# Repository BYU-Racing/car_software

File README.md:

# Car Software

## UML Diagram

See the UML diagram [here](/VehicleCode/CarUML_v1.0.md)

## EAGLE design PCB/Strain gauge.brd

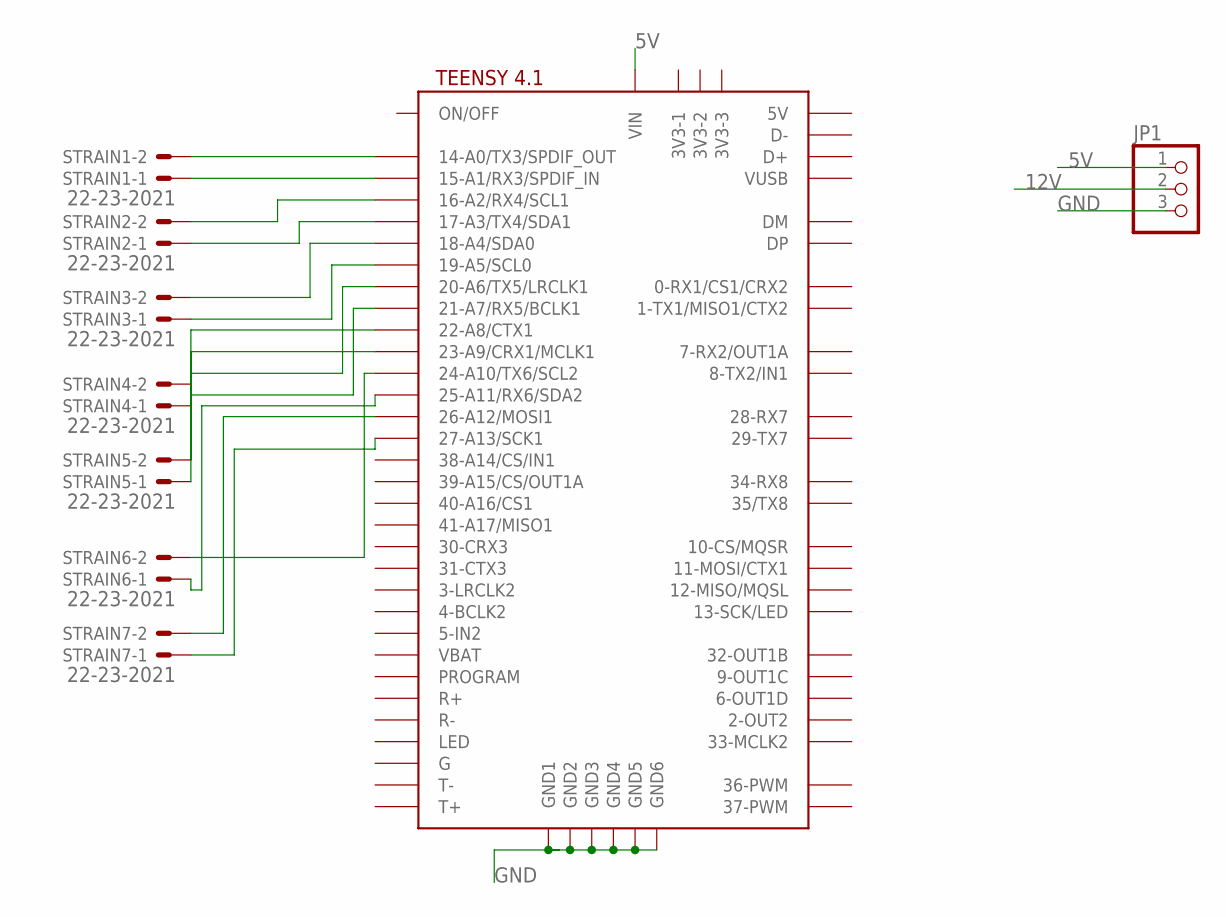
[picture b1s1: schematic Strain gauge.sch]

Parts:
JP1: PINHD-1X3; 1X03
STRAIN1, STRAIN2, STRAIN3, STRAIN4, STRAIN5, STRAIN6, STRAIN7: 22-23-2021
U$1: TEENSY41

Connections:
5V: JP1.1, U$1.VIN
12V: JP1.2
GND: JP1.3, U$1.GND1, U$1.GND2, U$1.GND3, U$1.GND4, U$1.GND5, U$1.GND6
unnamed: STRAIN1.2, U$1.14-A0/TX3/SPDIF_OUT
unnamed: STRAIN1.1, U$1.15-A1/RX3/SPDIF_IN
unnamed: STRAIN2.2, U$1.16-A2/RX4/SCL1
unnamed: STRAIN2.1, U$1.17-A3/TX4/SDA1
unnamed: STRAIN3.2, U$1.18-A4/SDA0
unnamed: STRAIN3.1, U$1.19-A5/SCL0
unnamed: STRAIN4.2, U$1.20-A6/TX5/LRCLK1
unnamed: STRAIN4.1, U$1.21-A7/RX5/BCLK1
unnamed: STRAIN5.2, U$1.22-A8/CTX1
unnamed: STRAIN5.1, U$1.23-A9/CRX1/MCLK1
unnamed: STRAIN6.2, U$1.24-A10/TX6/SCL2
unnamed: STRAIN6.1, U$1.25-A11/RX6/SDA2
unnamed: STRAIN7.2, U$1.26-A12/MOSI1
unnamed: STRAIN7.1, U$1.27-A13/SCK1

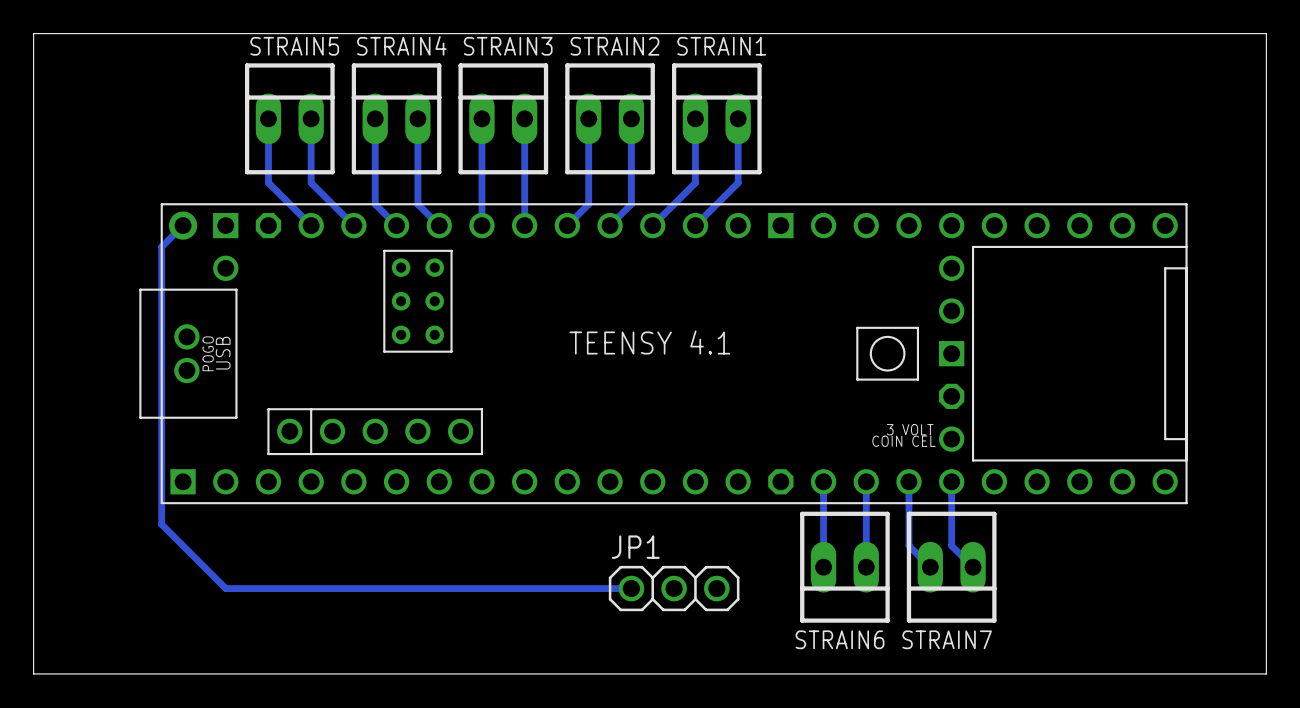
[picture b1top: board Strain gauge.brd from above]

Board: 2 copper layers, 73.3 x 38.1 mm, 9 parts (0 on the bottom side), 16 nets.

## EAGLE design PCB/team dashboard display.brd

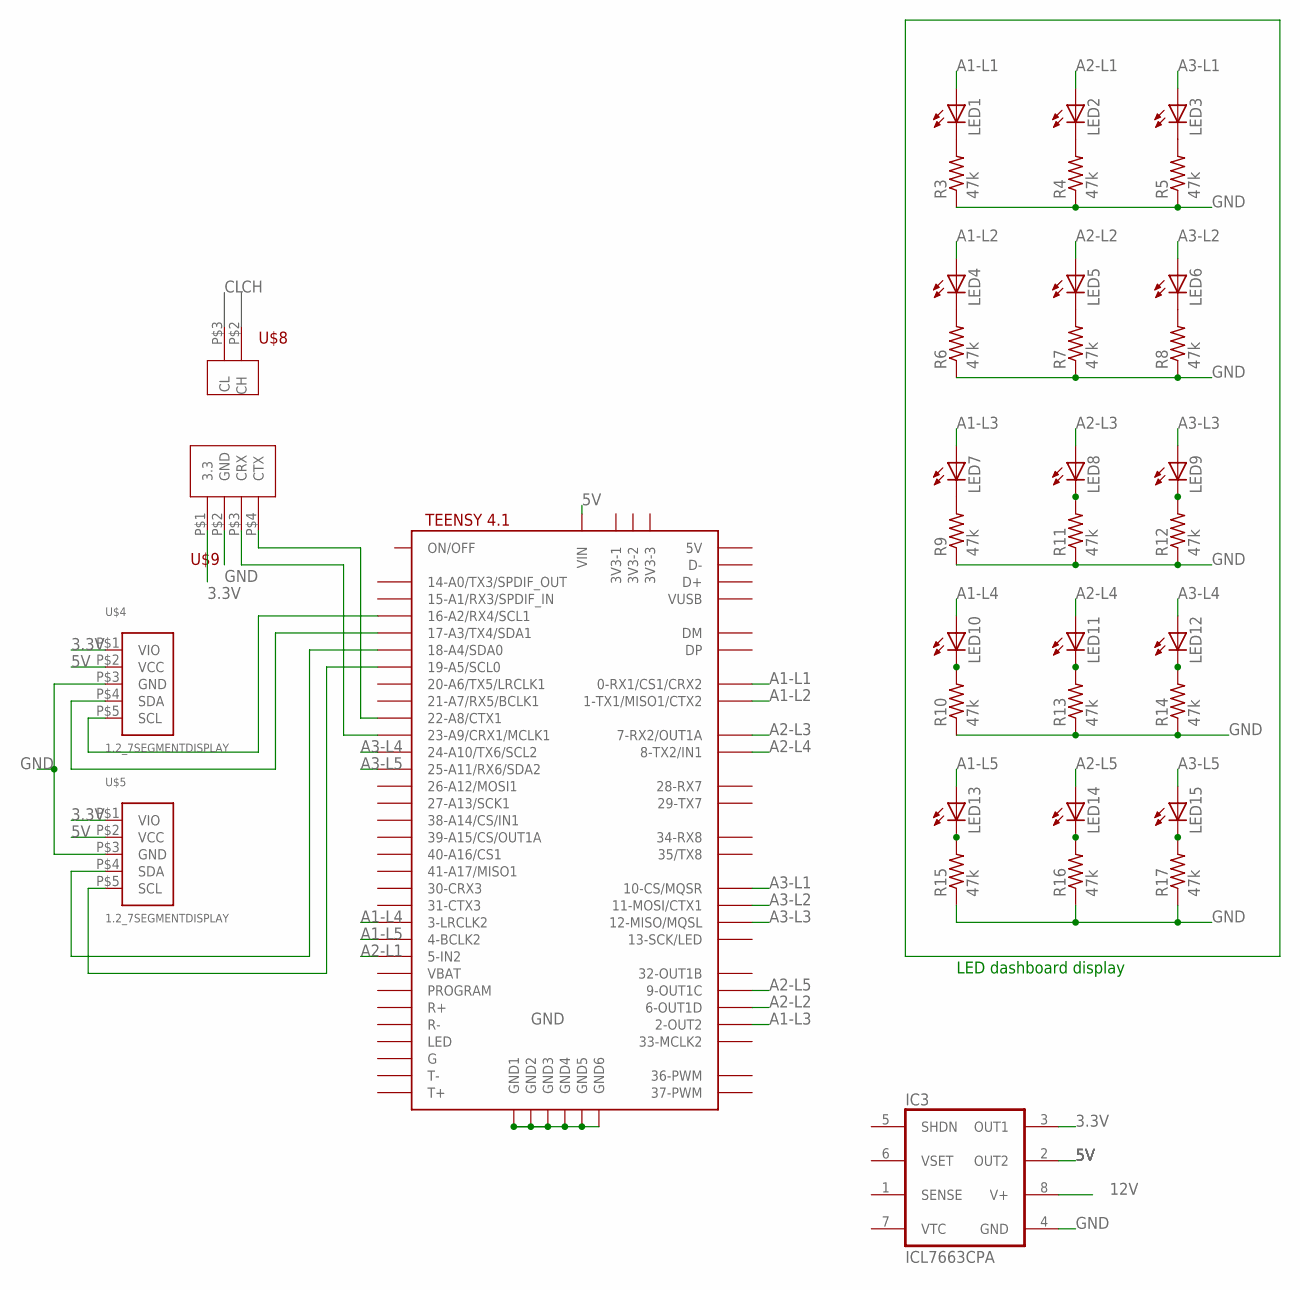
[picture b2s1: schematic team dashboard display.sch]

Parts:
IC3: ICL7663CPA; DIL08
LED1, LED2, LED3, LED4, LED5, LED6, LED7, LED8, LED9, LED10, LED11, LED12, LED13, LED14, LED15: LED3MM
R3, R4, R5, R6, R7, R8, R9, R10, R11, R12, R13, R14, R15, R16, R17: 47k; 0204/7
U$2: TEENSY41
U$4, U$5: 1.2_7SEGMENTDISPLAY; 5IL
U$8: CAN_BUS
U$9: CAN_TEE; CAN_TEN

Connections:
3.3V: IC3.3 (OUT1), U$4.P$1 (VIO), U$5.P$1 (VIO), U$9.P$1 (3.3)
5V: IC3.2 (OUT2), U$2.VIN, U$4.P$2 (VCC), U$5.P$2 (VCC); also elsewhere on the board
A1-L1: LED1.A, U$2.0-RX1/CS1/CRX2
A1-L2: LED4.A, U$2.1-TX1/MISO1/CTX2
A1-L3: LED7.A, U$2.2-OUT2
A1-L4: LED10.A, U$2.3-LRCLK2
A1-L5: LED13.A, U$2.4-BCLK2
A2-L1: LED2.A, U$2.5-IN2
A2-L2: LED5.A, U$2.6-OUT1D
A2-L3: LED8.A, U$2.7-RX2/OUT1A
A2-L4: LED11.A, U$2.8-TX2/IN2 (8-TX2/IN1)
A2-L5: LED14.A, U$2.9-OUT1C
A3-L1: LED3.A, U$2.10-CS\MQSR (10-CS/MQSR)
A3-L2: LED6.A, U$2.11-MOSI/CTX1
A3-L3: LED9.A, U$2.12-MISO/MQSL
A3-L4: LED12.A, U$2.24-A10/TX6/SCL2
A3-L5: LED15.A, U$2.25-A11/RX6/SDA2
GND: IC3.4 (GND), R3.1, R4.1, R5.1, R6.1, R7.1, R8.1, R9.1, R10.1, R11.1, R12.1, R13.1, R14.1, R15.1, R16.1, R17.1, U$2.GND1, U$2.GND2, U$2.GND3, U$2.GND4, U$2.GND5, U$2.GND6, U$4.P$3 (GND), U$5.P$3 (GND), U$9.P$2 (GND); also elsewhere on the board
unnamed: U$2.17-A3/TX4/SDA1, U$4.P$4 (SDA)
unnamed: U$2.16-A2/RX4/SCL1, U$4.P$5 (SCL)
unnamed: U$2.18-A4/SDA0, U$5.P$4 (SDA)
unnamed: U$2.19-A5/SCL0, U$5.P$5 (SCL)
unnamed: LED1.K (C), R3.2
unnamed: LED2.K (C), R4.2
unnamed: U$2.22-A8/CTX1, U$9.P$4 (CTX)
unnamed: U$2.23-A9/CRX1/MCLK1, U$9.P$3 (CRX)
unnamed: LED3.K (C), R5.2
unnamed: LED4.K (C), R6.2
unnamed: LED5.K (C), R7.2
unnamed: LED6.K (C), R8.2
unnamed: LED7.K (C), R9.2
unnamed: LED10.K (C), R10.2
unnamed: LED8.K (C), R11.2
unnamed: LED9.K (C), R12.2
unnamed: LED11.K (C), R13.2
unnamed: LED12.K (C), R14.2
unnamed: LED13.K (C), R15.2
unnamed: LED14.K (C), R16.2
unnamed: LED15.K (C), R17.2

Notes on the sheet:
LED dashboard display

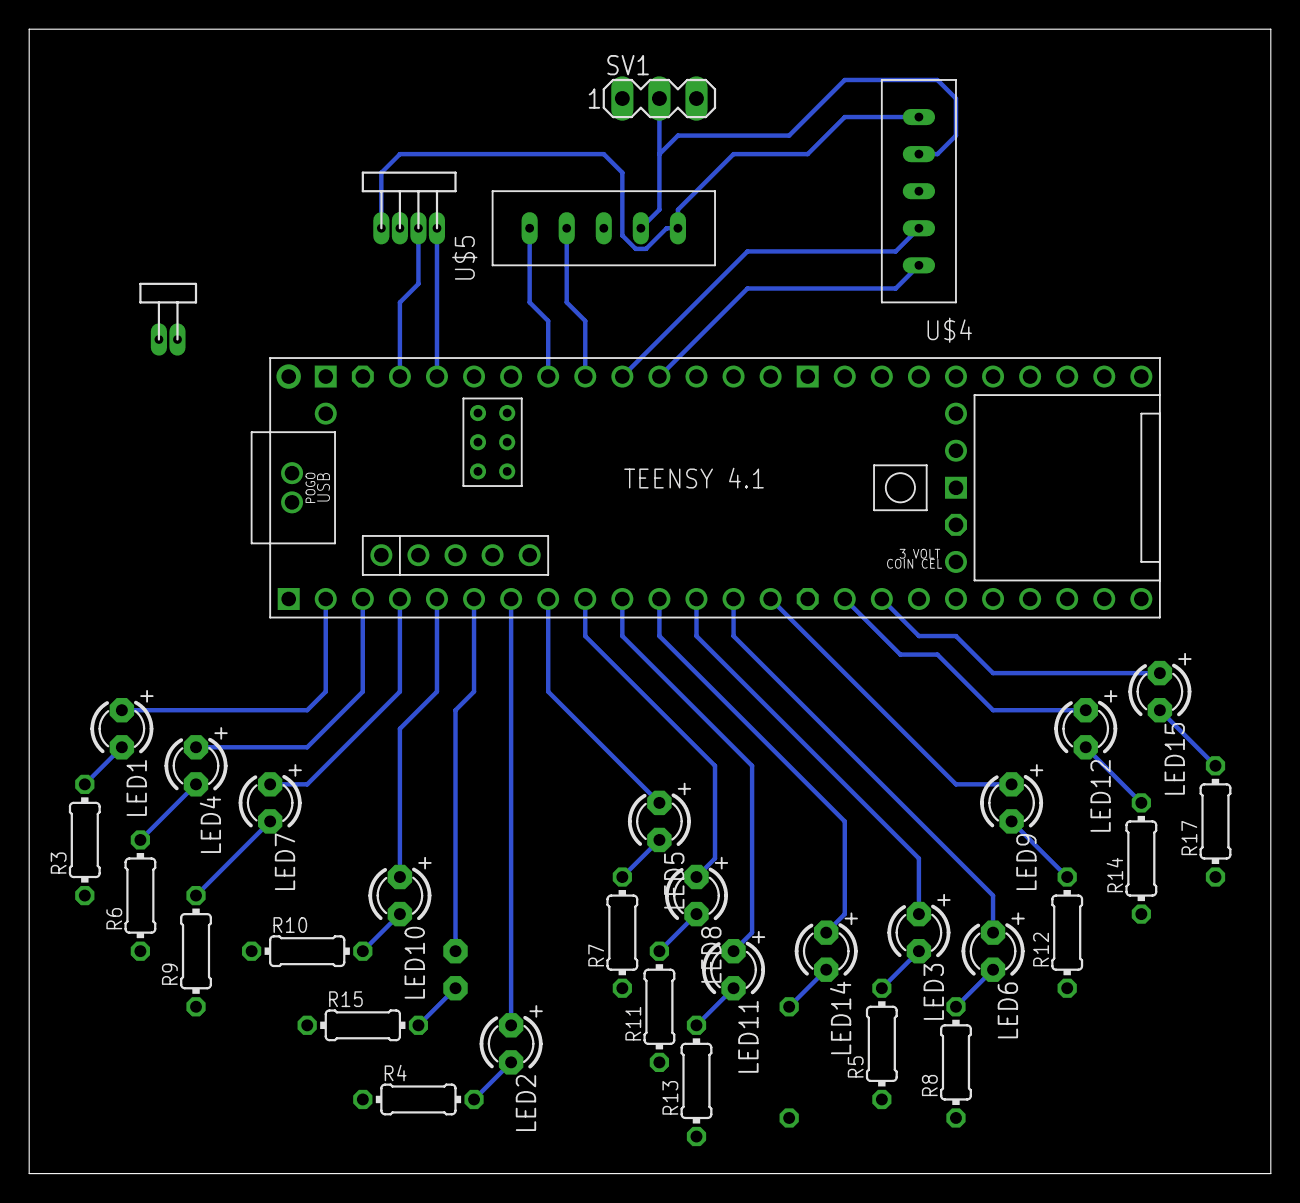
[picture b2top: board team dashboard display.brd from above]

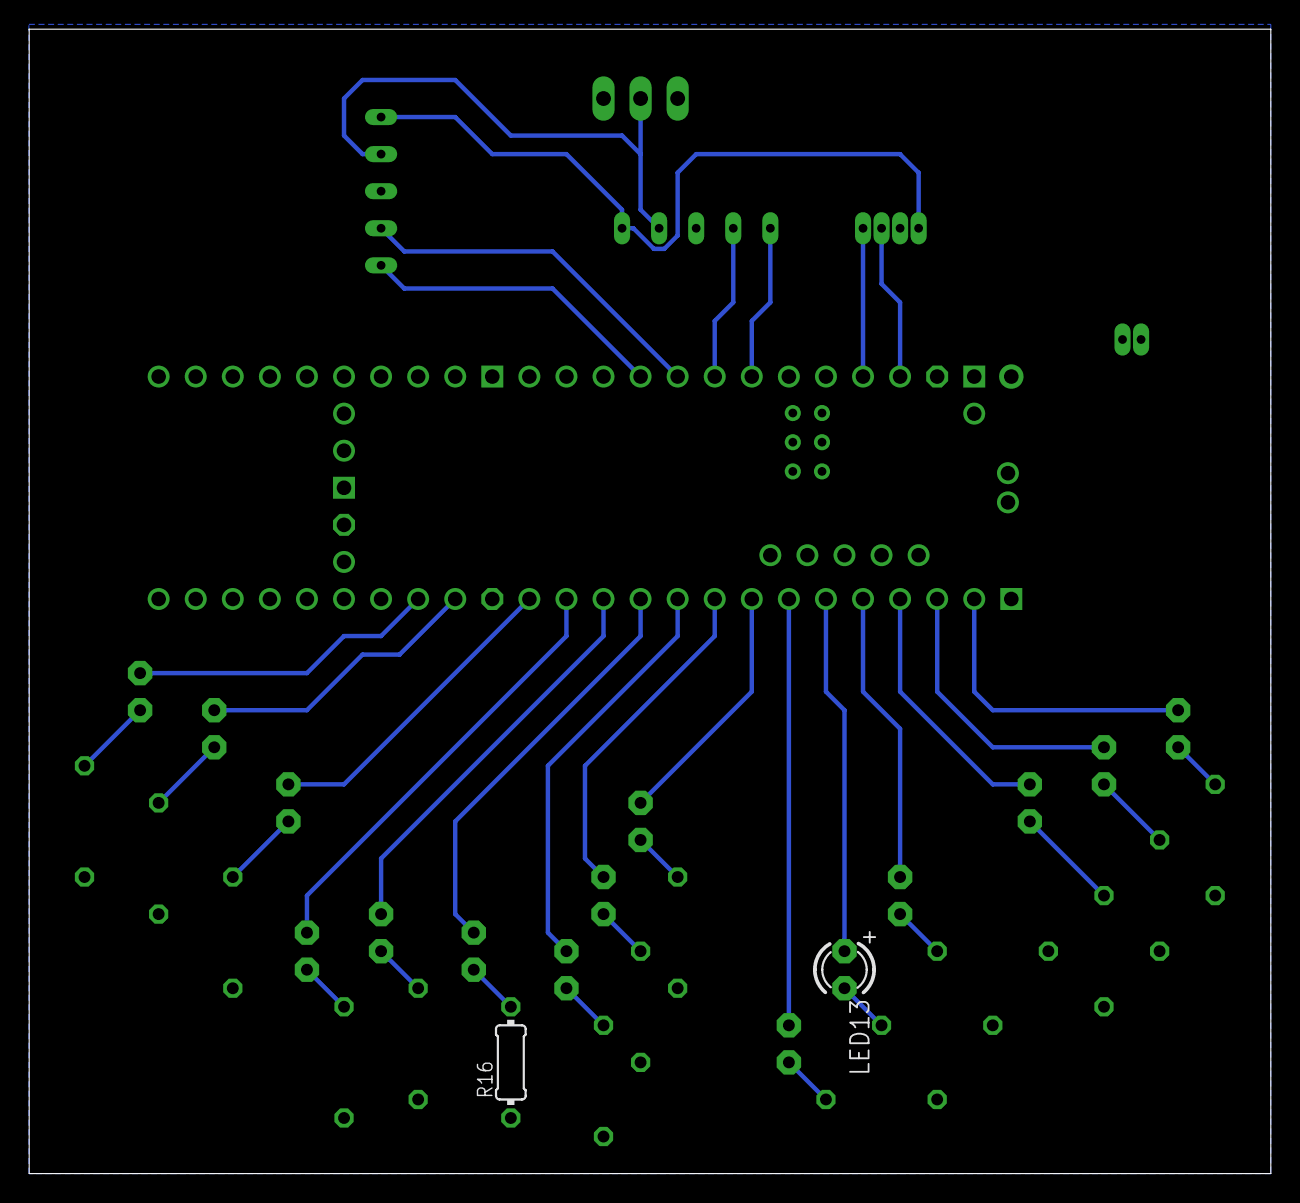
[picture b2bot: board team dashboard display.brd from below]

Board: 2 copper layers, 85.1 x 78.4 mm, 36 parts (2 on the bottom side), 39 nets.

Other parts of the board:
SV1: MA03-1

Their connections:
5V: SV1.2; also elsewhere on the board
GND: SV1.1; also elsewhere on the board

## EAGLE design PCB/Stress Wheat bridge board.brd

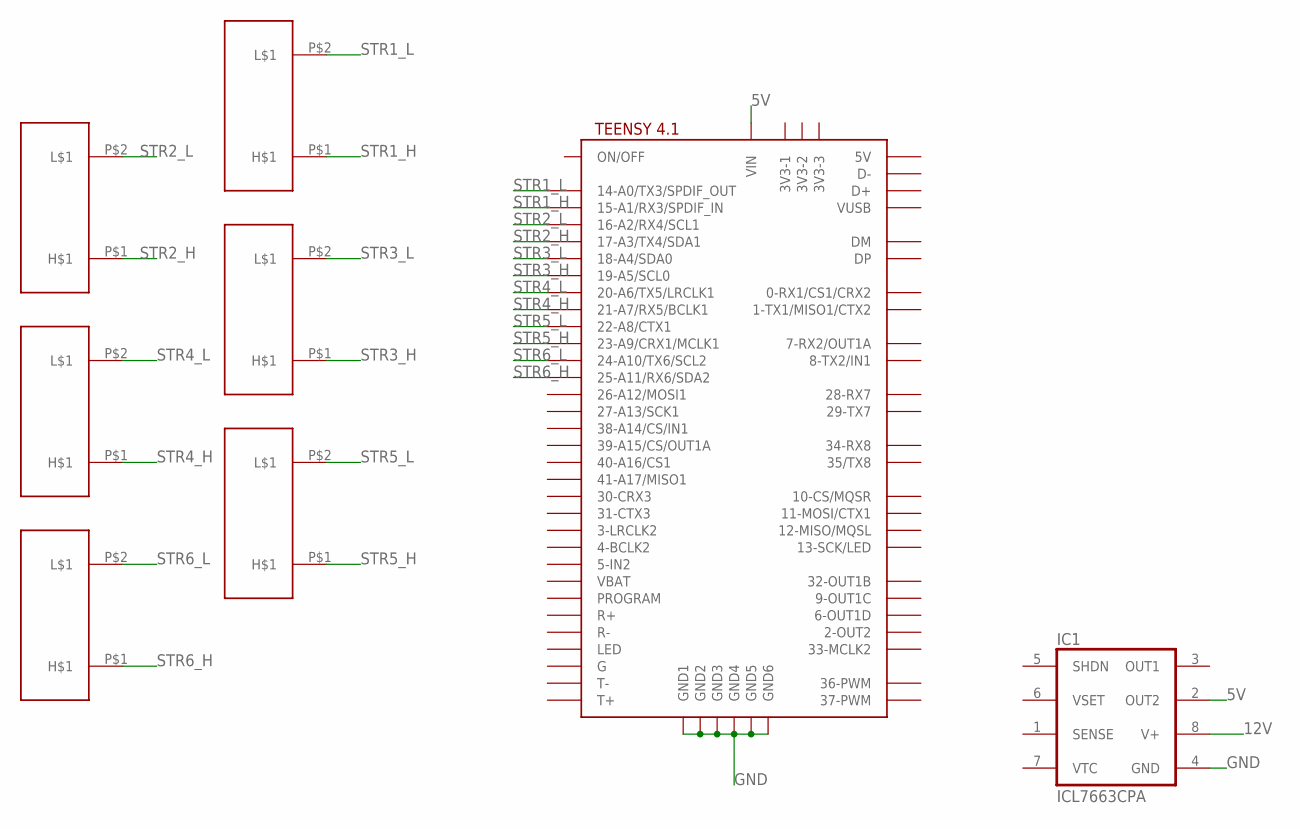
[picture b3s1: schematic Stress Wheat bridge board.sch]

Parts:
IC1: ICL7663CPA; DIL08
U$1, U$2, U$4, U$5, U$6, U$7: STR_GAUGE
U$3: TEENSY41

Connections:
5V: IC1.2 (OUT2), U$3.VIN
12V: IC1.8 (V+)
GND: IC1.4 (GND), U$3.GND1, U$3.GND2, U$3.GND3, U$3.GND4, U$3.GND5, U$3.GND6
STR1_H: U$1.P$1, U$3.15-A1/RX3/SPDIF_IN
STR1_L: U$1.P$2, U$3.14-A0/TX3/SPDIF_OUT
STR2_H: U$2.P$1, U$3.17-A3/TX4/SDA1
STR2_L: U$2.P$2, U$3.16-A2/RX4/SCL1
STR3_H: U$3.19-A5/SCL0, U$4.P$1
STR3_L: U$3.18-A4/SDA0, U$4.P$2
STR4_H: U$3.21-A7/RX5/BCLK1, U$5.P$1
STR4_L: U$3.20-A6/TX5/LRCLK1, U$5.P$2
STR5_H: U$3.23-A9/CRX1/MCLK1, U$6.P$1
STR5_L: U$3.22-A8/CTX1, U$6.P$2
STR6_H: U$3.25-A11/RX6/SDA2, U$7.P$1
STR6_L: U$3.24-A10/TX6/SCL2, U$7.P$2

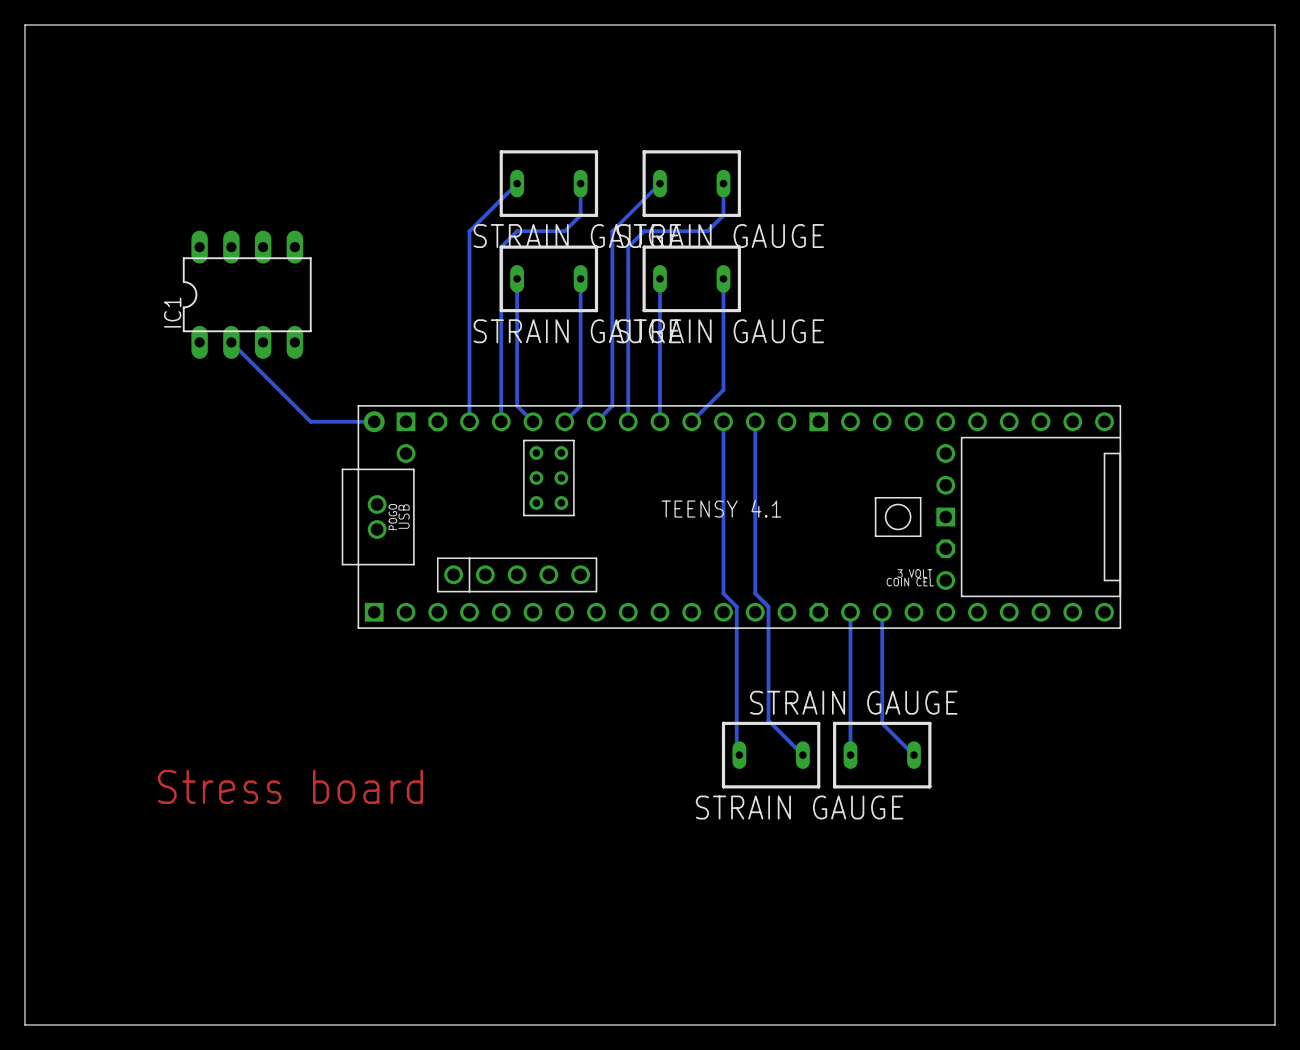
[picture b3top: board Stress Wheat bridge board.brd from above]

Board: 2 copper layers, 100.0 x 80.0 mm, 8 parts (0 on the bottom side), 14 nets.

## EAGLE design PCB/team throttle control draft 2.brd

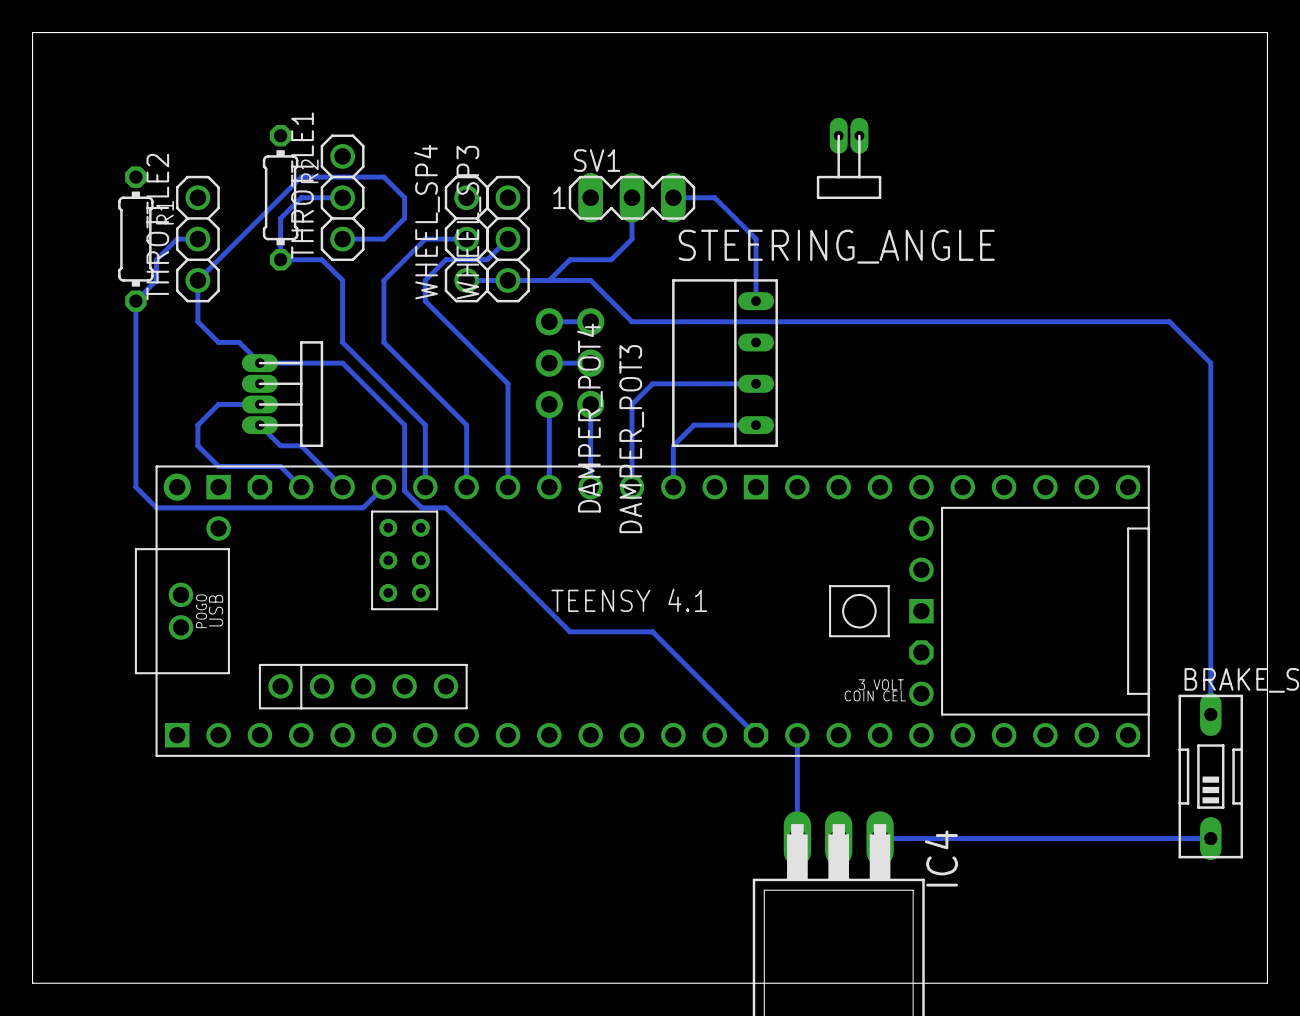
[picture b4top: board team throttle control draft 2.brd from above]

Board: 2 copper layers, 75.9 x 58.4 mm, 15 parts (0 on the bottom side), 18 nets.

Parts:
BRAKE_SW: EDG-01
DAMPER_POT3, DAMPER_POT4: 1X03-CLEANBIG
IC4: 7805T; TO220H
R1: 47k; 0204/7
R2: 470k; 0204/7
STEERING_ANGLE: ROTARY_ENCODER
SV1: MA03-1
THROTTLE1, THROTTLE2: 1X03
U$3: TEENSY41
U$10: CAN_BUS
U$11: CAN_TEE; CAN_TEN
WHEEL_SP3, WHEEL_SP4: 1X03

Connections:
3.3V: THROTTLE1.1, THROTTLE2.1, U$3.3V3-1, U$11.P$1
5V: STEERING_ANGLE.VCC, SV1.3
12V: BRAKE_SW.2, SV1.2, WHEEL_SP3.1, WHEEL_SP4.1
A2_2: DAMPER_POT3.3, U$3.16-A2/RX4/SCL1
A3_2: DAMPER_POT4.3, U$3.17-A3/TX4/SDA1
ACC_DATA_OUT_1: R2.2, THROTTLE1.2, U$3.20-A6/TX5/LRCLK1
ACC_DATA_OUT_2: R1.2, THROTTLE2.2, U$3.21-A7/RX5/BCLK1
BL_GND: DAMPER_POT3.2, DAMPER_POT4.2
BR_SW: IC4.3, U$3.24-A10/TX6/SCL2
BR_VCC: DAMPER_POT3.1, DAMPER_POT4.1
CRX_2: U$3.23-A9/CRX1/MCLK1, U$11.P$3
CTX_2: U$3.22-A8/CTX1, U$11.P$4
GND: IC4.2, R1.1, R2.1, STEERING_ANGLE.GND, SV1.1, THROTTLE1.3, THROTTLE2.3, U$3.GND1, U$3.GND2, U$3.GND3, U$3.GND4, U$3.GND5, U$3.GND6, WHEEL_SP3.3, WHEEL_SP4.3
unnamed: BRAKE_SW.1, IC4.1
T2_DP_1: STEERING_ANGLE.PH_A, U$3.14-A0/TX3/SPDIF_OUT
T2_DP_2: STEERING_ANGLE.PH_B, U$3.15-A1/RX3/SPDIF_IN
WH_SP3_D: U$3.18-A4/SDA0, WHEEL_SP3.2
WH_SP4_D: U$3.19-A5/SCL0, WHEEL_SP4.2

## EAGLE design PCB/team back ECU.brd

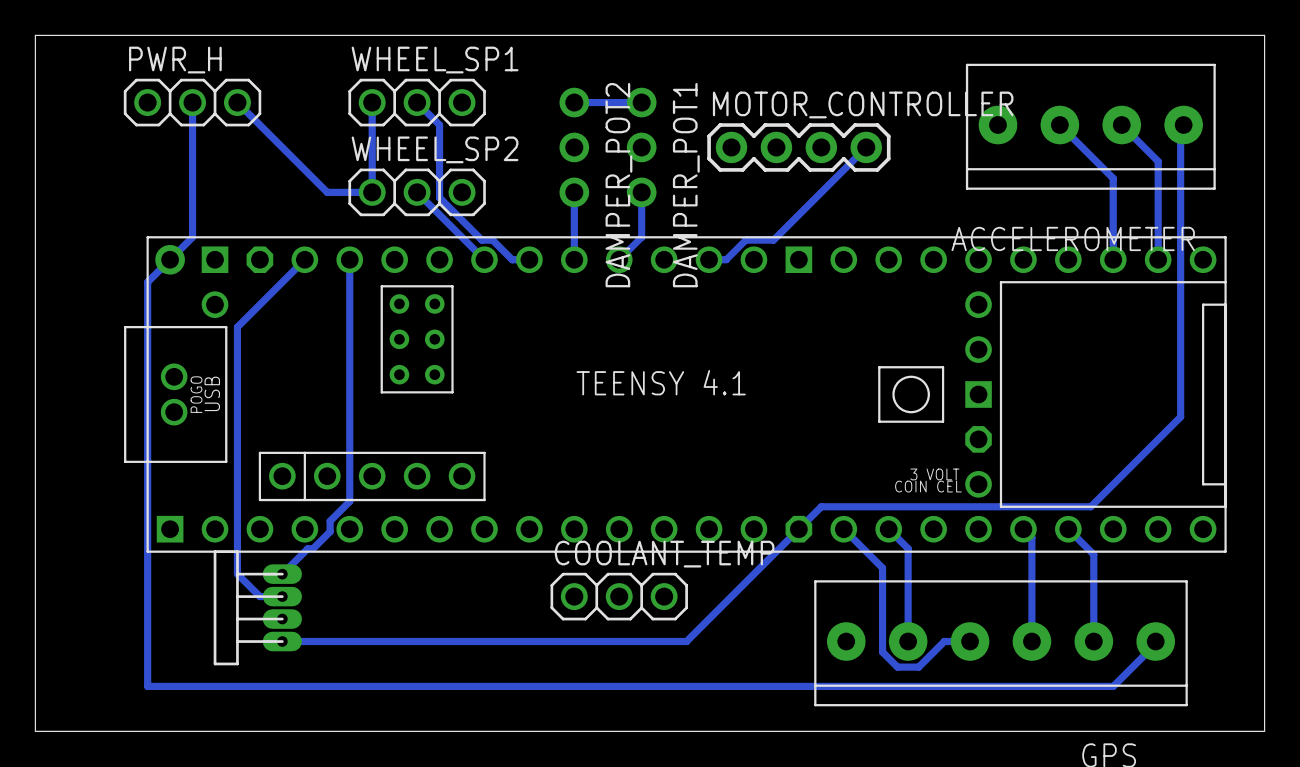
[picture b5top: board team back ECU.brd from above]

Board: 2 copper layers, 69.5 x 39.4 mm, 11 parts (0 on the bottom side), 18 nets.

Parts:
ACCELEROMETER: 1X4-3.5MM; 1X04-3.5MM
CAN1_TEE: CAN_TEE; CAN_TEN
COOLANT_TEMP: 1X03
DAMPER_POT1, DAMPER_POT2: 1X03-CLEANBIG
GPS: 1X06-3.5MM
MOTOR_CONTROLLER: 1X4-BIG; 1X04-BIG
PWR_H: 1X03
U$1: TEENSY41
WHEEL_SP1, WHEEL_SP2: 1X03

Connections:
3.3V: ACCELEROMETER.4, CAN1_TEE.P$1, U$1.3V3-1
5V: GPS.6, PWR_H.2, U$1.VIN
12V: PWR_H.3, WHEEL_SP1.1, WHEEL_SP2.1
A2: DAMPER_POT1.3, U$1.16-A2/RX4/SCL1
A3: DAMPER_POT2.3, U$1.17-A3/TX4/SDA1
A_MC: MOTOR_CONTROLLER.4, U$1.14-A0/TX3/SPDIF_OUT
BR_VCC: DAMPER_POT1.1, DAMPER_POT2.1
GND: ACCELEROMETER.1, CAN1_TEE.P$2, COOLANT_TEMP.3, DAMPER_POT1.2, DAMPER_POT2.2, GPS.1, MOTOR_CONTROLLER.1, PWR_H.1, U$1.GND1, U$1.GND2, U$1.GND3, U$1.GND4, U$1.GND5, U$1.GND6, WHEEL_SP1.3, WHEEL_SP2.3
unnamed: CAN1_TEE.P$3, U$1.23-A9/CRX1/MCLK1
unnamed: CAN1_TEE.P$4, U$1.22-A8/CTX1
RX: ACCELEROMETER.2, U$1.35-TX8
RX_2: GPS.5, U$1.29-TX7
SCL: GPS.3, U$1.24-A10/TX6/SCL2
SDA: GPS.2, U$1.25-A11/RX6/SDA2
TX: ACCELEROMETER.3, U$1.34-RX8
TX_2: GPS.4, U$1.28-RX7
WH_SP1_D: U$1.18-A4/SDA0, WHEEL_SP1.2
WH_SP2_D: U$1.19-A5/SCL0, WHEEL_SP2.2

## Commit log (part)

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2023-03-30 Fix resize bug, remove magic numbers, text resizes now
2023-03-30 Fix moving text bug
2023-03-30 Functional ready statement
2023-04-02 Attempt animation and fail
2023-04-03 uploaded example data
    follows the format sensorId, timestamp, data. This data comes from the accelerator pedal.
2023-04-04 Attempt to optimize and fail
2023-04-04 Code for sending and Receiving on 1 teensy
2023-04-06 Draft new data reading method
2023-04-08 Add requirements.txt
2023-04-16 Bought new transceiver, sends can msg to self
2023-04-17 Working on reading can message and spinning motor
2023-04-18 FUDGE YEAH
2023-04-18 Reorganization
2023-04-18 Improved Professionalism
2023-04-18 Included Authors
2023-06-03 Added Github_test.m as a test
2023-06-03 Added acceleration modeling Matlab files
2023-07-04 Added a 2nd vehicle profile
2023-07-04 Create README CHECKOUT
2023-07-04 Add files via upload
    original upload
2023-07-08 Teensy 4.1 layout
2023-07-08 Checkout
2023-07-09 Update README CHECKOUT
2023-07-09 7 Segment Displays add
2023-07-09 first draft layout 07-08
2023-09-19 UML Diagram
2023-09-19 trying to fix it
2023-09-20 UML Refinements
2023-09-22 individual boards 1
    Individual boards from the large build of the ECU and throttle control
2023-09-26 sync
2023-09-26 set up empty file structure
2023-09-26 draft input h files
2023-09-26 draft h files for output
2023-09-26 Adjusted file structure
2023-09-26 File Restructuring
2023-09-26 Created ECU Project
2023-09-26 Created other teensy project folders
2023-09-26 Reviewed Car UML
2023-09-26 Small Fix
2023-09-28 Added the team dashboard display schematic and the custom library used for most of the sensors in the schematics.
2023-09-28 clean up comments
2023-09-28 remove unnecessary cpp file
2023-09-28 Refinements
2023-09-28 TODO added
2023-09-29 AnalogSensor Initial work
2023-09-29 Header Comment info
2023-09-29 Comments to guide what to do next
2023-09-29 protected Sensor, analogSensor Update
2023-09-30 analogSensor Type Conversion Fixes
2023-10-02 Got rid of TODO
2023-10-02 Adjusted Sensor Class
2023-10-02 Changes for analog sensor
2023-10-02 team throttle control draft 1
    First draft of the throttle control for review and comments. I am planning on doing a more comprehensive redesign in the coming days.
2023-10-03 team throttle control draft 2
    An updated team throttle control design, streamlined and better routing.
2023-10-03 SensorData class wrk
2023-10-03 draft datacollector
2023-10-03 add docstrings and update uml
2023-10-05 begin .cpp file
2023-10-05 implementing more uart.cpp file
2023-10-05 changes for two serial reads uart.cpp
2023-10-05 Checked
2023-10-06 create and wire dash schematic
2023-10-06 intial commit
2023-10-06 test
2023-10-06 json changes
2023-10-06 changes to uart.cpp
2023-10-08 Draft dashboard.cpp
2023-10-08 add todo
2023-10-08 fix memory leaks and add docstrings
2023-10-09 Initial Servo code
2023-10-09 Started working on Car Class
2023-10-09 Checked and added comments
2023-10-09 added necessary files to data collector 1
2023-10-09 Started data colloctor 1 teensy code
2023-10-09 Reviewed
2023-10-09 Small syntax thing
2023-10-09 It was missing two connections so this is now fixed and fully operating design
2023-10-10 minor changes for merge, dallin
2023-10-10 experiment with object for sensor id
2023-10-10 cleanest id implementation so far
2023-10-10 ready to test all except constructor
2023-10-11 Added Calibration and Testing Folder
2023-10-14 Added Screen Ic2
2023-10-16 Stress board for Wheat bridge and edits
    Created the Wheat bridge board with the different stress gauges in the F-E library. There were some minor edits that the other boards needed as well.
2023-10-16 Updated 10-16-23
2023-10-16 Edited out some issues (10-16-32)
2023-10-16 Added purdy picture (10-16-23)
2023-10-18 small update on throttle
2023-10-24 draft digital sensor
2023-10-27 progess
2023-11-03 Fixed some stuff
2023-11-07 Sensor Classes tested. Needs destructors
2023-12-08 simplified readytocheck
2023-12-08 added 3-pin header to dashboard display pcb/schematic. optimized component layout and shrunk pcb board by 40-50%
2023-12-11 Altium conversion
    Converted all PCB files from EAGLE to Altium. Many bugs need to be ironed out on each board/schem but it's likely a simple process
2024-01-09 Updated ECU and Strain Gauge board
2024-01-10 Remove voltage regulator. Add 3-pin header. Connect 3.3V wire
2024-01-11 ThrottleWrite written
2024-01-11 add receive platio
2024-01-11 Updated sensordata.cpp
2024-01-12 remove priority
2024-01-12 fix names error
2024-01-15 debugging
2024-01-15 Send Throttle
2024-01-15 successful test
2024-01-15 write doc strings
2024-01-15 Progress on redundant throttle
2024-01-17 Retry polygon to fix GND signal
    didn't work.
2024-01-17 redundancy on throttle
2024-01-18 PCB update and Altium file creation from Eagle
2024-01-20 draft error class
2024-01-20 add error class
2024-01-20 see if this format works
2024-01-20 try again
2024-01-22 second draft errors
2024-01-23 revert error class
2024-01-24 debug new code
2024-01-30 add throttle sensor
2024-01-30 draft car class
2024-01-31 pret
2024-02-02 fixed sd card bug
2024-02-09 debug with hv
2024-02-09 update after testing
2024-02-09 copy pltfrmio
2024-02-09 Reroute dash display with 10mil traces. Repour polygon.
    the 4 pin header U$9 is throwing clearance errors, not sure why. will check with ELC tomorrow
2024-02-14 make global
2024-02-14 progress on car
2024-02-14 debug car
2024-02-14 Initial Changes to Actuator, LEDArray, Dashboard. Tested Working w/ Landon
2024-02-16 Shrink 4 pin pads to meet constraint requirements. Make gerber files. Zip them
2024-02-16 Update to the PCB designs
2024-02-21 fix logging
2024-02-21 Addition of Screen Class, Tested with Actuator. Ready to merge to main
2024-02-21 Small Change with sensorID identifications
2024-02-22 removed files
    Got rid of any files that arent about testing or writing the software that will be on the car
2024-02-22 Readme update
2024-02-23 simple blink code to test teensys/connectivity
2024-02-23 Fix ECU pcb trace widths. Generate and zip gerber files.
2024-02-23 update altium
2024-02-23 Teensy testing files
2024-02-24 works
2024-02-24 created switch project
2024-02-24 digital sensor class working
2024-02-25 fix car logging
2024-02-25 refactor class
2024-02-25 draft sync script
2024-02-26 updates script
2024-02-26 formatting
2024-02-27 finish car class
2024-02-27 newest car class
2024-02-27 Throttle ready
2024-02-27 Project That was used to test Actuator. These files DO NOT have the formatting changes that are in the vehicle code folders
2024-02-28 replace files
2024-02-28 set up int test
2024-02-28 fixed can_test folder
2024-02-28 test multiple sensor logging and fail
2024-02-29 testing with toy
2024-02-29 motor go brrrr
2024-03-01 Synced ActuatorTestBuild into Github
2024-03-01 fix csv naming
2024-03-01 Added ActuatorTestBuild to the Github
2024-03-01 add testing class
2024-03-01 work pls
2024-03-01 test 3 led arrays
2024-03-01 Created a platform.io project to hardcode the motorcontroller CAN data
2024-03-03 debug timestamp and log errors
2024-03-03 sync with latest version
2024-03-05 adjusted can sniff
2024-03-05 cleaned up repo
2024-03-05 modified .gitignore
2024-03-05 updated .gitignore
2024-03-05 VROOOOM
2024-03-05 logstate on opens datafile
2024-03-06 sync for testing
2024-03-07 C:/Users/dalli/source/repos/BYURacing/FormulaE/VehicleCode/TestingAndCalibration/DashboardTest/src/Dashboard.cpp
2024-03-07 syncronize updates
2024-03-07 add docstrings
2024-03-07 motor start signal
2024-03-09 throttle torque limit
2024-03-16 throttle adjustments
2024-03-22 log on car
2024-03-23 faster
2024-03-27 Untested NEW LED ARRAY battery percentage
2024-03-27 Small tweaks
2024-03-27 BatteyTemp lights
2024-03-27 changes to 0.5 C differences based off datasheet
2024-03-29 Small changes to parameters
2024-03-29 flag and comment changes
2024-03-30 LED methods changed private
2024-03-30 fixed comment
2024-03-30 simplify
2024-03-31 UML Diagram Updates
2024-04-03 LED Array fixes
2024-04-06 Dashboard testing changes + new LED array Tested
2024-04-09 horn
2024-04-11 Battery Temp Light parameter changes
2024-04-14 Throttle changes that are running on car
2024-04-14 Gotta go to church
2024-04-14 Some bug fixes. Should be compadible with dataCollector
2024-04-14 Remove whiteSpacve
2024-04-15 eror
2024-04-15 nnnnn
2024-04-16 debug and fail
2024-04-17 smallChanges
2024-04-17 Error checking code
2024-04-17 small more error fixes
2024-04-17 small comment fix
2024-04-20 Quick Throttle Change
2024-04-22 fixed can_sniff
2024-04-22 enhance switch and work
2024-04-23 First Changes to the DataCollector
2024-04-23 DataCollectorChanges
2024-04-23 Small Changes
2024-04-23 Timeout trip fix
2024-04-23 Spacing fix
2024-04-23 Remove fixed TODO
2024-04-24 finished horn class
2024-04-24 add constructor with soundPin passed in
2024-04-24 Small Sensor Changes :)
2024-04-24 Some changes
2024-04-24 Analog Sensor Changes
2024-04-27 can_sniff
2024-04-28 Pull request changes
2024-04-28 bugFix
2024-05-03 3 teensys on car
2024-05-03 moved testing to full car software folder
2024-05-04 Car Class Changes to run with it!
2024-05-04 TESTING FOR SOFTWARE BRAKE (TESTED WORKING)
2024-05-04 Car Update Testing
2024-05-04 Testing and Calibration ON CAR CODE
2024-05-04 Added Changes to the Car Class
2024-05-06 Header tweaks
2024-05-06 Fixed 0 start
2024-05-06 Baseline tweak
2024-05-06 Testing Adjustment
2024-05-07 Changes to file formatting
2024-05-07 EV 4.7.2 Rules Compliance Change
2024-05-09 PR changes
2024-05-13 small adjustments
2024-05-13 Wiring harness notes
2024-05-17 wiring harness update
2024-05-17 wiring update
2024-05-18 Horn tweak
2024-05-18 Car Class Horn Change
2024-05-18 Wording fix
2024-05-18 timing fix
2024-05-18 Wiring standard
2024-05-18 cleanup and calibration
2024-05-18 rearrange
2024-05-18 agreement between files
2024-05-18 Some more file consistency
2024-05-18 Analog Sensor
2024-05-18 Bug Fixes
2024-05-18 brake calibrated
2024-05-19 New Sensor Just Dropped
2024-05-19 Tractive Changes to DC
2024-05-22 analog change
2024-05-22 oopsies
2024-05-24 Tractive Sensor now looks for 6ms for BMS signal
2024-05-30 Tractive & DC Changes
2024-05-30 Data Collector Changes and addition of Tractive Sensor
2024-05-30 Timing Change
2024-05-31 Tractive Sensor Tweaks
2024-05-31 Project FIle tweaks
2024-05-31 Max torque brake sensor check
2024-06-05 horn testing
2024-06-08 stuff
2024-06-09 adjusted calibration
2024-06-09 The Magi are involved in almost every operation and are seen as one of NERVs most valuable assets, taking priority over every other function in NERV HQ
2024-06-11 davids changes
2024-06-11 Pins wrong for Dashboard
2024-06-12 Dear lord please be the last non tune push
2024-07-04 Last Competition Changes
2024-07-04 2024 Layout Changes
2024-07-04 2024 Dev Code + placeholders
2024-07-04 DataCollector Health Check and notes
2024-07-04 Notes
2024-07-05 ECU Diagnostic read
2024-07-05 Brake error state bug fix
2024-08-10 Learning the ropes
2024-08-12 More tested Dashboard control funcitons
2024-08-13 Global fixes and drivestate logic
2024-08-13 DriveState reset Tweak
2024-08-13 var renames
2024-08-14 ECU Compiles
2024-08-14 ECU2 Project ready to test
2024-08-16 Integration Test Prep
2024-08-16 Cal values able to be set from function
2024-08-16 Throttle cal method break up
2024-08-17 Auto Throttle Calibration routing
2024-08-17 Bug fix
2024-08-18 Integration Testing
2024-08-20 Testing + error changes
2024-08-20 Mock EV Active ntegration Testing
2024-08-20 start fault error throw
2024-08-22 ECU + Throttle error changes
2024-08-22 Test of some dashboard update changers
2024-08-24 Memoize Dashboard
2024-08-24 Created project
2024-08-24 Test Project
2024-08-24 Hail mary at auto throttle calibration
2024-08-24 Ready to test!!
2024-08-24 testChange
2024-09-06 running on car
2024-09-06 Memory allocation fix
2024-09-06 Clean up
2024-09-06 Small Memory Fix
2024-09-07 First Push For Drive Modes
2024-09-07 Missing vals
2024-09-07 More controls
2024-09-07 Dashboard Drive Mode
2024-09-07 Reset changes
2024-09-09 Dashboard logic tweak
2024-09-09 More logic tweaks
2024-09-10 const expr change
2024-09-10 Removal of delay
2024-09-12 Sensor Data Library Update
2024-09-12 WOX init
